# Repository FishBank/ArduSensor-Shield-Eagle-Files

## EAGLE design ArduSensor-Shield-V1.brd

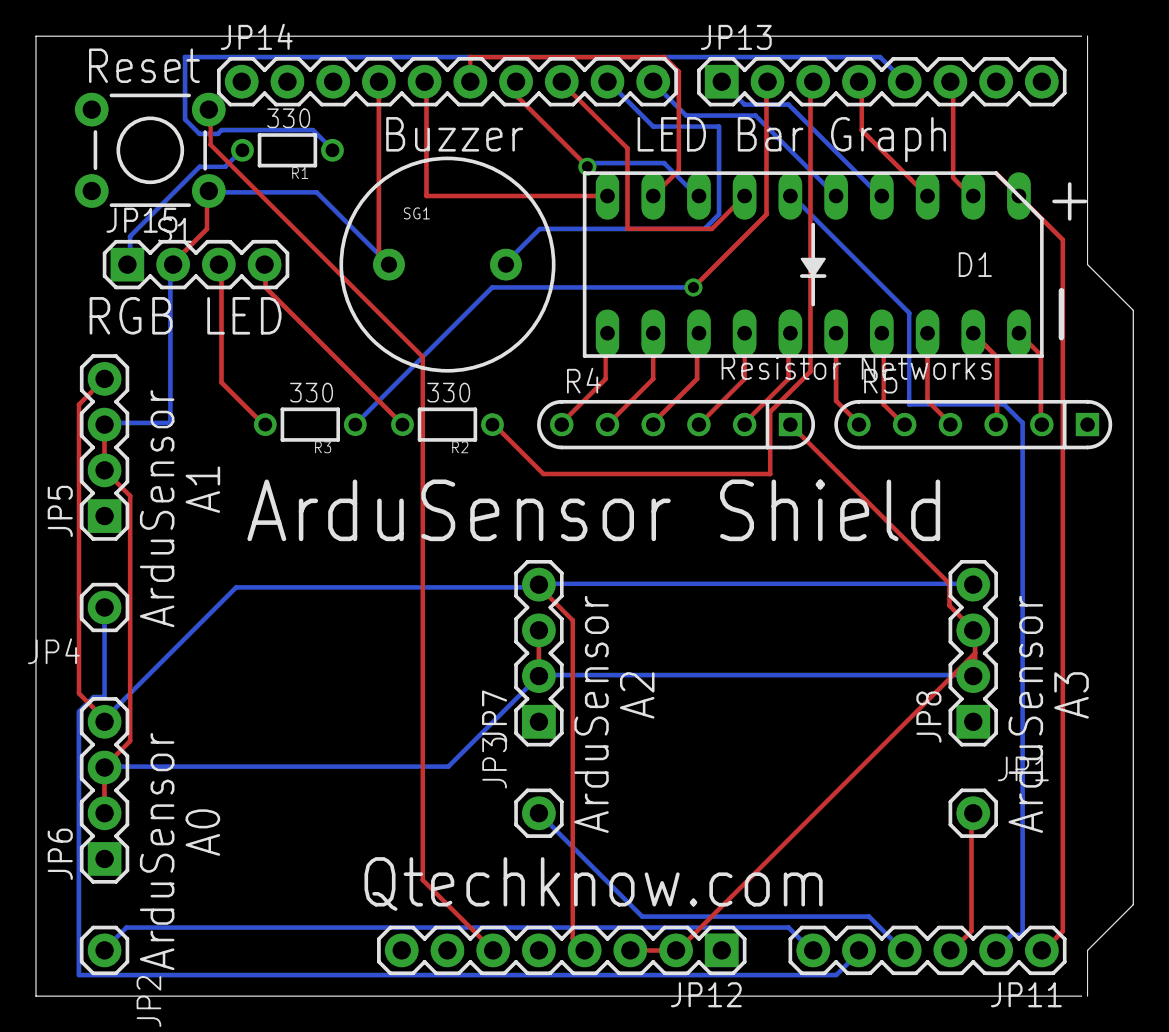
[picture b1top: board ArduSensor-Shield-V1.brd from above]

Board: 2 copper layers, 61.0 x 53.3 mm, 21 parts (0 on the bottom side), 34 nets.

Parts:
D1: LED_BARGAPH_10
JP1, JP2, JP3, JP4: M01PTH; 1X01
JP5, JP6, JP7, JP8, JP15: 1X04
JP11: 1X06
JP12, JP13: 1X08
JP14: M10"; 1X10
R1, R2, R3: 1/6W-RES
R4, R5: RPACK-SIP-PTH-5
S1: SWITCH-MOMENTARY-2PTH; TACTILE-PTH
SG1: BUZZERPTH; BUZZER-12MM

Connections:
5V: JP5.4, JP6.4, JP7.4, JP8.4, JP12.4
GND: JP5.2, JP5.3, JP6.2, JP6.3, JP7.2, JP7.3, JP8.2, JP8.3, JP12.2, JP12.3, JP14.4, JP15.2, R4.P$1, S1.1, SG1.-
unnamed: D1.5, JP14.10
unnamed: JP13.5, R1.1
unnamed: JP13.2, R3.1
unnamed: JP13.3, R2.1
unnamed: JP14.9, SG1.+
unnamed: D1.7, JP14.8
unnamed: JP15.1, R1.2
unnamed: JP2.1, JP11.6
unnamed: JP4.1, JP11.5
unnamed: JP1.1, JP11.3
unnamed: JP15.4, R2.2
unnamed: D1.6, JP11.2
unnamed: JP3.1, JP11.4
unnamed: D1.9, JP14.6
unnamed: D1.11, R4.P$6
unnamed: D1.12, R4.P$5
unnamed: D1.13, R4.P$4
unnamed: D1.14, R4.P$3
unnamed: D1.15, R4.P$2
unnamed: D1.10, JP14.5
unnamed: D1.16, R5.P$6
unnamed: D1.17, R5.P$5
unnamed: D1.18, R5.P$4
unnamed: D1.19, R5.P$3
unnamed: D1.20, R5.P$2
unnamed: JP15.3, R3.2
unnamed: D1.3, JP13.4
unnamed: D1.2, JP13.6
unnamed: D1.1, JP11.1
unnamed: D1.4, JP13.1
unnamed: JP12.6, S1.3
unnamed: D1.8, JP14.7

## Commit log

2012-07-13 Schematic

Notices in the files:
parts and their libraries:
SFE LED: Licensing: CC v3.0 Share-Alike You are welcome to use this library for commercial purposes.
